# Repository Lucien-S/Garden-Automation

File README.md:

# Garden Automation — ESP32

Automated garden watering system based on ESP32, soil moisture sensors (RS485/Modbus), solenoid valves, and MQTT over WiFi.

Youtube link: [ https://youtube.com/shorts/rQiWS8xde-I?feature=share ](https://youtu.be/8DQGsPcLfHw)

KiCad files are available in the folder /kicad

---

## Hardware

| Component | Details |
|-----------|---------|
| MCU | ESP32-WROOM-32D |
| Moisture sensors | RS485 Modbus (x2), addresses 0x01 and 0x02 |
| Solenoid valves | 3× EV (EV1, EV2, EV3) driven via GPIO |
| Pump | 1× driven via GPIO |
| Display | SSD1306 OLED 128×32, I2C |
| Communication | WiFi SoftAP + MQTT |

### Pin Mapping

| Pin | Function |
|-----|----------|
| GPIO 23 | Pump |
| GPIO 19 | EV1 |
| GPIO 22 | EV2 |
| GPIO 3 | EV3 |
| GPIO 32 | OLED SDA |
| GPIO 33 | OLED SCL |
| GPIO 16 | RS485 RX |
| GPIO 17 | RS485 TX |

---

## Software

### Dependencies

All libraries are loaded from `/Users/rascarcapac/Documents/Arduino/libraries` via `lib_extra_dirs` in `platformio.ini`.

| Library | Purpose |
|---------|---------|
| Adafruit SSD1306 | OLED display |
| Adafruit GFX | Graphics primitives |
| PubSubClient | MQTT client |
| RTClib | DS3231 RTC (optional, not used in this branch) |

### platformio.ini

```ini
[env:esp32dev]
platform = espressif32
board = esp32dev
framework = arduino

monitor_speed = 115200
monitor_echo = yes
monitor_filters = send_on_enter

lib_extra_dirs = /Users/rascarcapac/Documents/Arduino/libraries
```

---

## Architecture

### Serial communication

Two separate modes are used depending on context:

- **Wizard (setup)** — character-by-character read loop with `yield()` to feed the FreeRTOS watchdog. Blocking by design since it waits for human input.
- **Runtime (loop)** — non-blocking char-by-char buffer. A complete command is processed only when `\n` is received.

### Runtime commands (Serial or MQTT)

Format: `CMD` or `CMD:value`

| Command | Effect |
|---------|--------|
| `WATER:1` | Start watering cycle on EV1 |
| `WATER:2` | Start watering cycle on EV2 |
| `WATER:3` | Start watering cycle on EV3 |
| `STOP` | Stop active watering cycle immediately |
| `STATUS` | Print current state to Serial |
| `RESET_DAILY` | Reset daily water usage counter |

The same `processRuntimeCommand()` function handles both Serial and MQTT input.

### MQTT topics

| Topic | Direction | Content |
|-------|-----------|---------|
| `garden/valve/command` | subscribe | `WATER:1`, `STOP`, etc. |
| `garden/sensors/sensor1/humidity` | publish | float, e.g. `42.3` |
| `garden/sensors/sensor1/temperature` | publish | float |
| `garden/sensors/sensor2/humidity` | publish | float |
| `garden/sensors/sensor2/temperature` | publish | float |
| `garden/pump/state` | publish | `ON` or `OFF` |

### WiFi

The ESP32 runs as a **SoftAP** (access point), not a station. Other devices connect to it.

| Parameter | Value |
|-----------|-------|
| SSID | `Colloc` |
| IP | `192.168.4.1` |
| MQTT broker expected at | `192.168.4.2` |

---

## Watering logic

- Watering triggers when a sensor reads below **30% humidity**
- Each valve has a **cooldown period** of 2 minutes between cycles
- A **daily water budget** is computed from reservoir size (10 L) divided by configured number of days
- Usage is persisted in NVS (flash) and survives reboots
- Maximum single cycle duration: 30 seconds

---

## Configuration wizard

On first boot (or if NVS is not calibrated), a serial wizard guides through:

1. Sensor calibration (dry / wet reference values)
2. Plumbing check
3. Sensor → valve mapping
4. Watering days configuration
5. Hardware test (each valve + pump for 5s)

Type `r` at any prompt to restart the wizard from the beginning.

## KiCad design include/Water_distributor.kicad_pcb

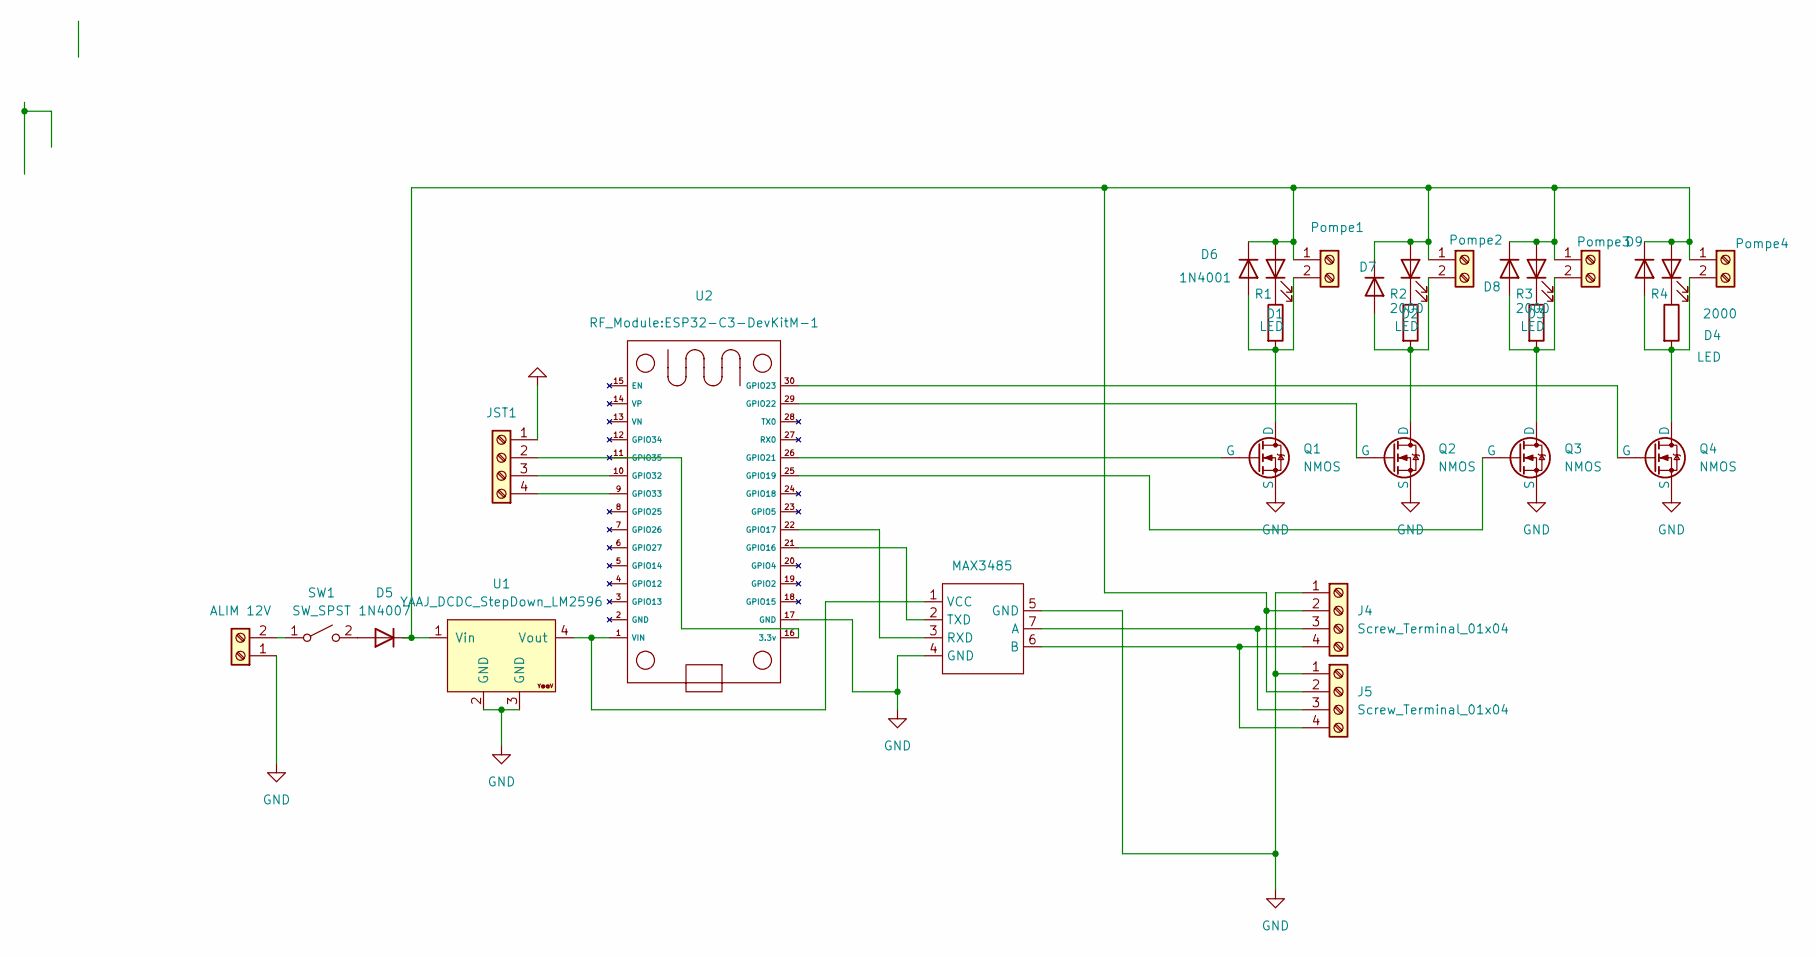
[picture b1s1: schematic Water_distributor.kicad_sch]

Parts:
D1, D2, D3, D4: LED; LED_0805_2012Metric_Pad1.15x1.40mm_HandSolder
D5: 1N4007; D_P600_R-6_P20.00mm_Horizontal
D6, D7, D8, D9: 1N4001; D_DO-41_SOD81_P10.16mm_Horizontal
J1: ALIM 12V; PhoenixContact_MCV_1,5_2-G-3.81_1x02_P3.81mm_Vertical
J4, J5: Screw_Terminal_01x04; TerminalBlock_Xinya_XY308-2.54-4P_1x04_P2.54mm_Horizontal
JST1: Screw_Terminal_01x04; JST_XH_B04B-XH-A_04x2.50mm_Straight
MAX3485: MAX3485
Pompe1, Pompe2, Pompe3, Pompe4: Screw_Terminal_01x02; TerminalBlock_Xinya_XY308-2.54-2P_1x02_P2.54mm_Horizontal
Q1, Q2, Q3, Q4: NMOS; TO-220-3_Vertical
R1, R2, R3, R4: 2000; R_0805_2012Metric_Pad1.20x1.40mm_HandSolder
SW1: SW_SPST; lever_switch
U1: YAAJ_DCDC_StepDown_LM2596; DCDC_LM2596
U2: ESP32-C3-DevKitM-1

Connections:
GND: J1.1, J4.1, J5.1, JST1.1 (GND), MAX3485.4 (GND), MAX3485.5 (GND), Q1.3 (S), Q2.3 (S), Q3.3 (S), Q4.3 (S), U1.2 (GND), U1.3 (GND), U2.17 (GND)
unnamed: D1.2 (A), D2.2 (A), D3.2 (A), D4.2 (A), D5.1 (K), D6.1 (K), D7.1 (K), D8.1 (K), D9.1 (K), J4.2, J5.2, Pompe1.1, Pompe2.1, Pompe3.1, Pompe4.1, U1.1 (Vin)
unnamed: D1.1 (K), R1.1
unnamed: D2.1 (K), R2.1
unnamed: D3.1 (K), R3.1
unnamed: D4.1 (K), R4.1
unnamed: D5.2 (A), SW1.2 (B)
unnamed: D6.2 (A), Pompe1.2, Q1.1 (D), R1.2
unnamed: D7.2 (A), Pompe2.2, Q2.1 (D), R2.2
unnamed: D8.2 (A), Pompe3.2, Q3.1 (D), R3.2
unnamed: D9.2 (A), Pompe4.2, Q4.1 (D), R4.2
unnamed: J1.2, SW1.1 (A)
unnamed: J4.3, J5.3, MAX3485.7 (A)
unnamed: J4.4, J5.4, MAX3485.6 (B)
unnamed: JST1.4 (Pin_1), U2.9 (GPIO33)
unnamed: JST1.3 (Pin_2), U2.10 (GPIO32)
unnamed: JST1.2 (Vin), U2.16 (3.3v)
unnamed: MAX3485.3 (RXD), U2.22 (GPIO17)
unnamed: MAX3485.2 (TXD), U2.21 (GPIO16)
unnamed: MAX3485.1 (VCC), U1.4 (Vout), U2.1 (VIN)
unnamed: Q1.2 (G), U2.26 (GPIO21)
unnamed: Q2.2 (G), U2.29 (GPIO22)
unnamed: Q3.2 (G), U2.25 (GPIO19)
unnamed: Q4.2 (G), U2.30 (GPIO23)

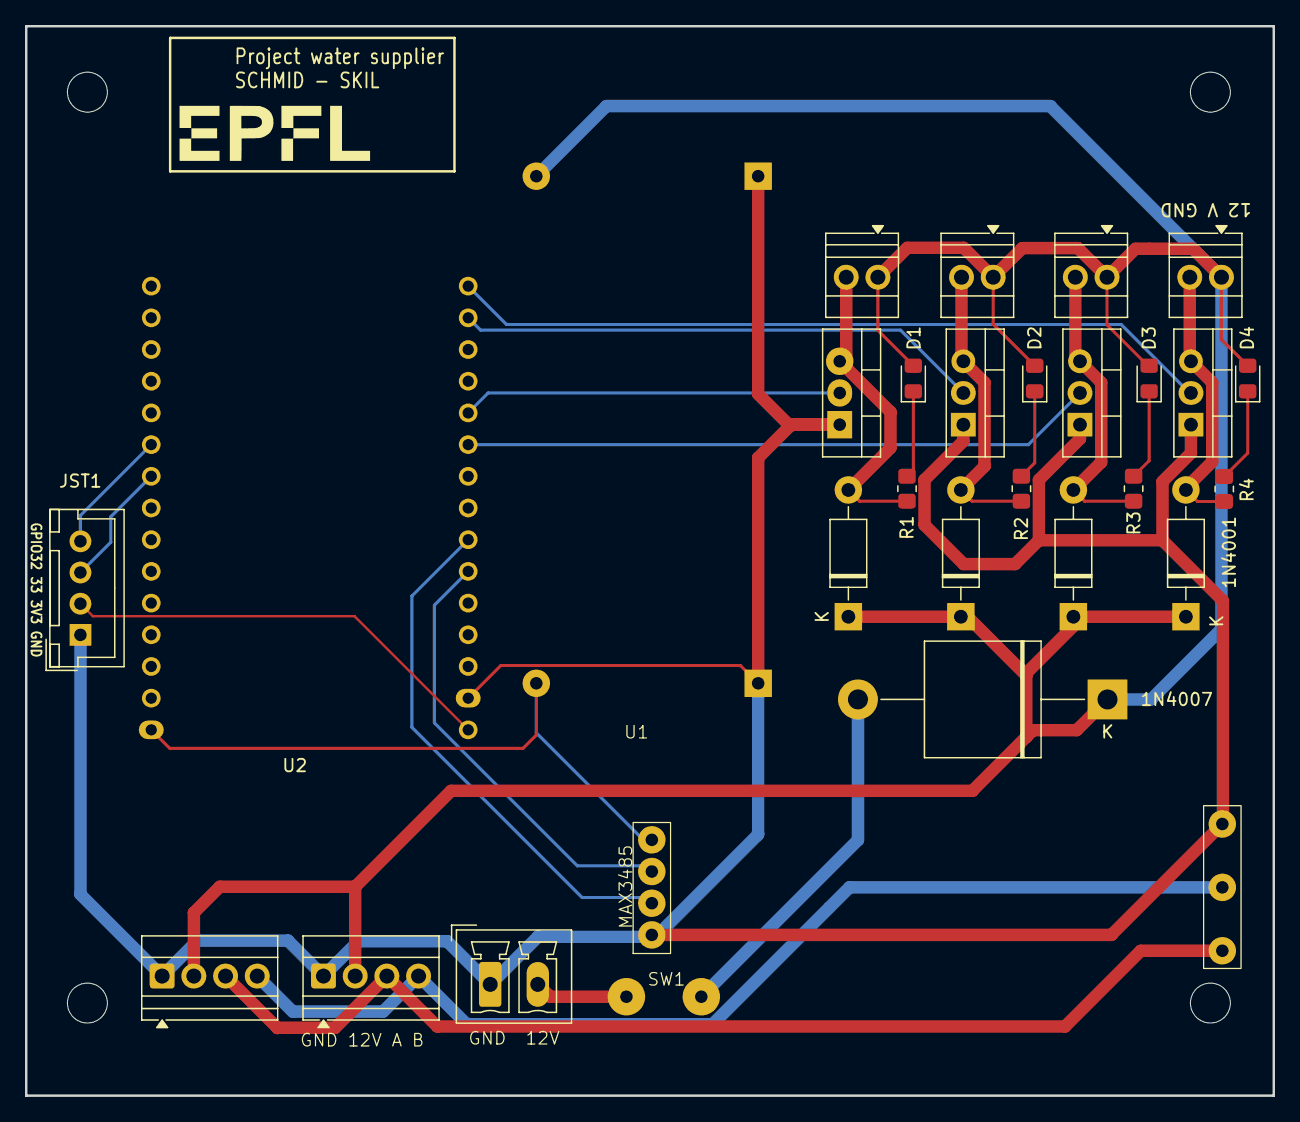
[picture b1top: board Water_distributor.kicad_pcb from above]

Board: 2 copper layers, 100.0 x 85.7 mm, 29 parts (0 on the bottom side), 24 nets.

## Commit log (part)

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2026-03-02 Adding CLAUDE.md architecture instructions file. It is read before any changes by Claude and creates a branch when the change is major.
2026-03-05 Adding KiCad info
2026-03-05 Zip and kicad files
    All layers, schematics and footprints are available.
2026-03-11 Fix YouTube link formatting in README
    Updated YouTube link format in README.
